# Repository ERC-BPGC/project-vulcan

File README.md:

# Project VULCAN

Project VULCAN is an open humanoid robotics platform focused on expressive human-robot interaction through modular mechanical, electronic, and AI-driven subsystems. It is a humanoid robot facial structure that can interact with humans — tracking faces, expressing emotions, hearing and speaking.

## Current Status

Actively undergoing infrastructure modernization and subsystem stabilization before next-generation expansion.

## Architecture Principles
* Atomic modular subsystems.
* Minimal cross-module interference.
* Hardware/software separation.
* Scalable pipelines for future contributors.
* Experiment isolation via `experiments/`.

## System Pipeline Overview

```text
 Microphone Input
        ↓
 Speech-to-Text
        ↓
 Emotion + Context Fusion
        ↓
 LLM / RAG Pipeline
        ↓
 Response Generation
        ↓
 TTS + Mouth Movement + Facial Expressions

```

## Features
* **Eyes** — Independent 2-axis eyeball motion, eyelids, and gaze tracking via embedded cameras.
* **Mouth** — Lip movement synced with speech and emotional expressions.
* **Eyebrows** — Up/down motion to complement expressions.
* **Neck** — 2-axis motion (horizontal 360° + vertical tilt).
* **Hearing & Speech** — Microphone array for sound localisation, speech recognition, and TTS output.
* **Vision** — Face detection, gaze estimation, emotion recognition (FER), hand-wave detection.
* **LLM Integration** — RAG-augmented responses via GPT.

## Demos

*(GIF previews of eye tracking, blinking, mouth articulation, and emotion response coming soon!)*

* [Eye, eyelid & eyebrow subsystem](https://www.youtube.com/watch?v=uqxhR49N3ws) — asymmetric eyeball motion with cameras, blinking, and brow movement.
* [Mouth subsystem](https://www.youtube.com/watch?v=Ke2lJfY4haM) — lip articulation for speech and emotion.
* [Neck subsystem](https://www.youtube.com/watch?v=GJRW8hP-Jcs) — full pan and tilt.

## Hardware Stack
* ESP32-CAM vision nodes.
* Arduino Mega servo controller.
* Custom servo PCB.
* Embedded microphones.
* Dual-camera eye subsystem.

## Subsystems

### Mechanical

* **Eye, eyelid & eyebrow subsystem** — asymmetric eyeball motion with cameras, blinking, and brow movement.
* **Mouth subsystem** — lip articulation for speech and emotion.
* **Neck subsystem** — full pan and tilt.

### Software

* **`software/vision/`** — face detection, gaze estimation (`t_gaze.py`), emotion recognition (`m_model.py`, `m_expression.py`), hand-wave detection.
* **`software/speech/`** — speech-to-text, TTS, voice selection.
* **`software/llm/`** — GPT interface and RAG pipeline for context-aware responses.
* **`software/core/`** — main driver (`vulcan.py`, `vulcan2.py`) coordinating all subsystems.

### Electronics

* **Servo PCB (ESP32 & Mega variants)** — custom KiCad boards in `electronics/pcb/`.
* **ESP32-CAM firmware** — `electronics/firmware/camera_esp/`.
* **Arduino servo firmware** — `electronics/firmware/serial_arduino/`.

## Repository Structure

```text
project-vulcan/
├── docs/                   # Install guides (CUDA, OpenCV, dlib), diagrams
├── software/
│   ├── core/               # Main entry points
│   ├── vision/             # CV modules
│   ├── speech/             # STT / TTS
│   ├── llm/                # GPT + RAG pipeline
│   │   └── rag/
│   ├── data/               # Knowledge base files for RAG
│   ├── utils/              # Shared helpers
│   ├── tools/              # Diagnostic scripts (check mic, list cameras)
│   ├── experiments/        # Prototypes and WIP scripts
│   ├── models/             # Model weights (gitignored — see models/README.md)
│   ├── archive/            # Deprecated code
│   └── requirements.txt
├── electronics/
│   ├── pcb/                # KiCad projects
│   ├── firmware/           # Arduino / ESP32 sketches
│   └── scripts/            # Python hardware-communication scripts
└── mechanical/             # CAD files (SolidWorks, Fusion, Blender, STL)
    ├── Eye_subsystem/
    ├── Mouth_Subsystem/
    ├── Head Structure/
    ├── Neck Base/
    └── base_holder/

```

> **Model weights** are not tracked in git — see ```software/models/README.md``` for download links. <br>
> **Install guides** for CUDA, OpenCV, and dlib are in ```docs/```

## Getting Started

```bash
# Install Python dependencies
pip install -r software/requirements.txt

# Download model weights (see software/models/README.md), then run
python software/core/vulcan2.py

```

## Contributor Guidelines

* New features should be isolated into modules.
* Avoid editing archived or legacy systems.
* Experimental work belongs in `software/experiments/`.
* Shared utilities belong in `software/utils/`.
* All hardware communication layers must remain abstracted.

## Roadmap

* ROS2 migration.
* Improved facial animation pipeline.
* Real-time multimodal emotion fusion.
* Autonomous interaction routines.
* Enhanced gaze tracking.
* Full conversational memory system.

## Built With

* [Python](https://www.python.org/)
* [OpenCV](https://opencv.org/)
* [dlib](http://dlib.net/)
* [LangChain](https://www.langchain.com/) / [OpenAI](https://openai.com/)
* [KiCad](https://www.kicad.org/)
* [ROS](https://www.ros.org/)

## Downloading all the dependencies for running auto folder
- Make sure cmake and cuda are already downloaded before doing this
- Download the reurequirements.txt file
- pip install -r requirements.txt

## Limitations

* The robot covers only the structure above the neck — no full-body mobility.

## Core Contributors

* [Parth Shah](https://github.com/Parth-Shah-Tool-Kit)
* [Ritwik Sharma](https://github.com/Maker-Rat)
* [Sharvil Potdar](https://github.com/CipherWielder1104)
* [Aryan Goyal]
* [Kevin B. Matthew]
* Indrajit Mandal
* [Anirudh Singh Air](https://github.com/bodsvei)
* [Ayush R. Srivastava]
* [Aditya Kushwaha](https://github.com/Adityakushwaha2006)
* [Vedant Vakharia](https://github.com/vedantvakharia)
* [Rajas Kasar]

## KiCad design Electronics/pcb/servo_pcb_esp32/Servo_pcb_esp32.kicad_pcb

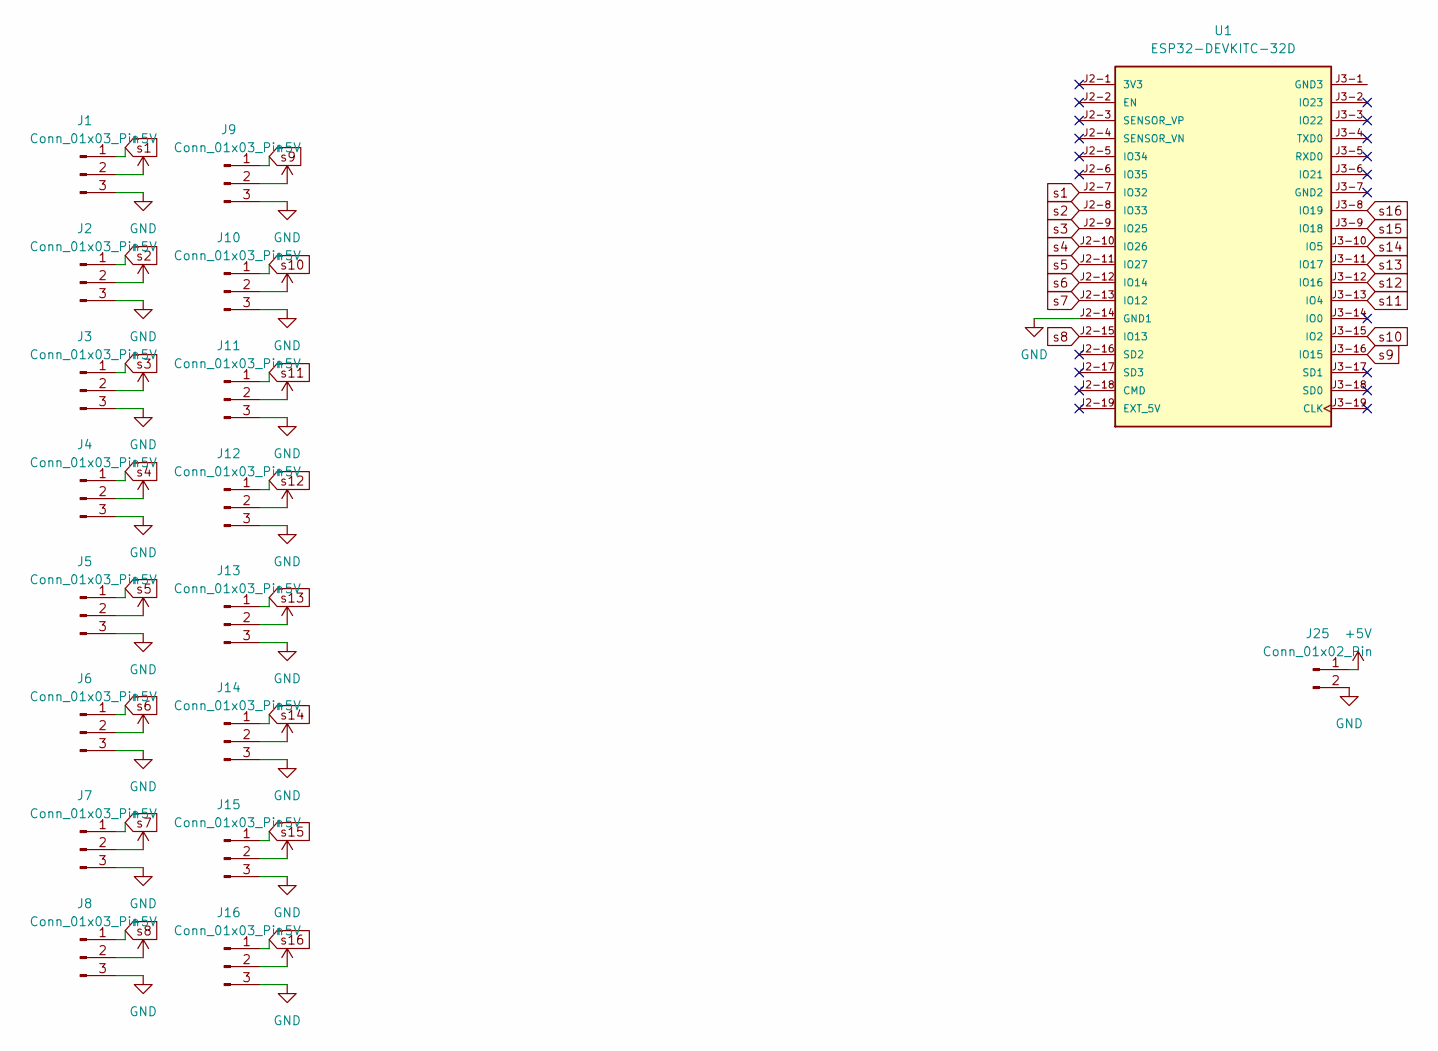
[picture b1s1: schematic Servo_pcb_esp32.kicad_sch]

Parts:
J1, J2, J3, J4, J5, J6, J7, J8, J9, J10, J11, J12, J13, J14, J15, J16: Conn_01x03_Pin; PinHeader_1x03_P2.54mm_Vertical
J25: Conn_01x02_Pin; AMASS_XT60-M_1x02_P7.20mm_Vertical
U1: ESP32-DEVKITC-32D; MODULE_ESP32-DEVKITC-32D; PARTREV V4

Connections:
+5V: J1.2, J2.2, J3.2, J4.2, J5.2, J6.2, J7.2, J8.2, J9.2, J10.2, J11.2, J12.2, J13.2, J14.2, J15.2, J16.2, J25.1
GND: J1.3, J2.3, J3.3, J4.3, J5.3, J6.3, J7.3, J8.3, J9.3, J10.3, J11.3, J12.3, J13.3, J14.3, J15.3, J16.3, J25.2, U1.J2-14 (GND1)
s1: J1.1, U1.J2-7 (IO32)
s2: J2.1, U1.J2-8 (IO33)
s3: J3.1, U1.J2-9 (IO25)
s4: J4.1, U1.J2-10 (IO26)
s5: J5.1, U1.J2-11 (IO27)
s6: J6.1, U1.J2-12 (IO14)
s7: J7.1, U1.J2-13 (IO12)
s8: J8.1, U1.J2-15 (IO13)
s9: J9.1, U1.J3-16 (IO15)
s10: J10.1, U1.J3-15 (IO2)
s11: J11.1, U1.J3-13 (IO4)
s12: J12.1, U1.J3-12 (IO16)
s13: J13.1, U1.J3-11 (IO17)
s14: J14.1, U1.J3-10 (IO5)
s15: J15.1, U1.J3-9 (IO18)
s16: J16.1, U1.J3-8 (IO19)

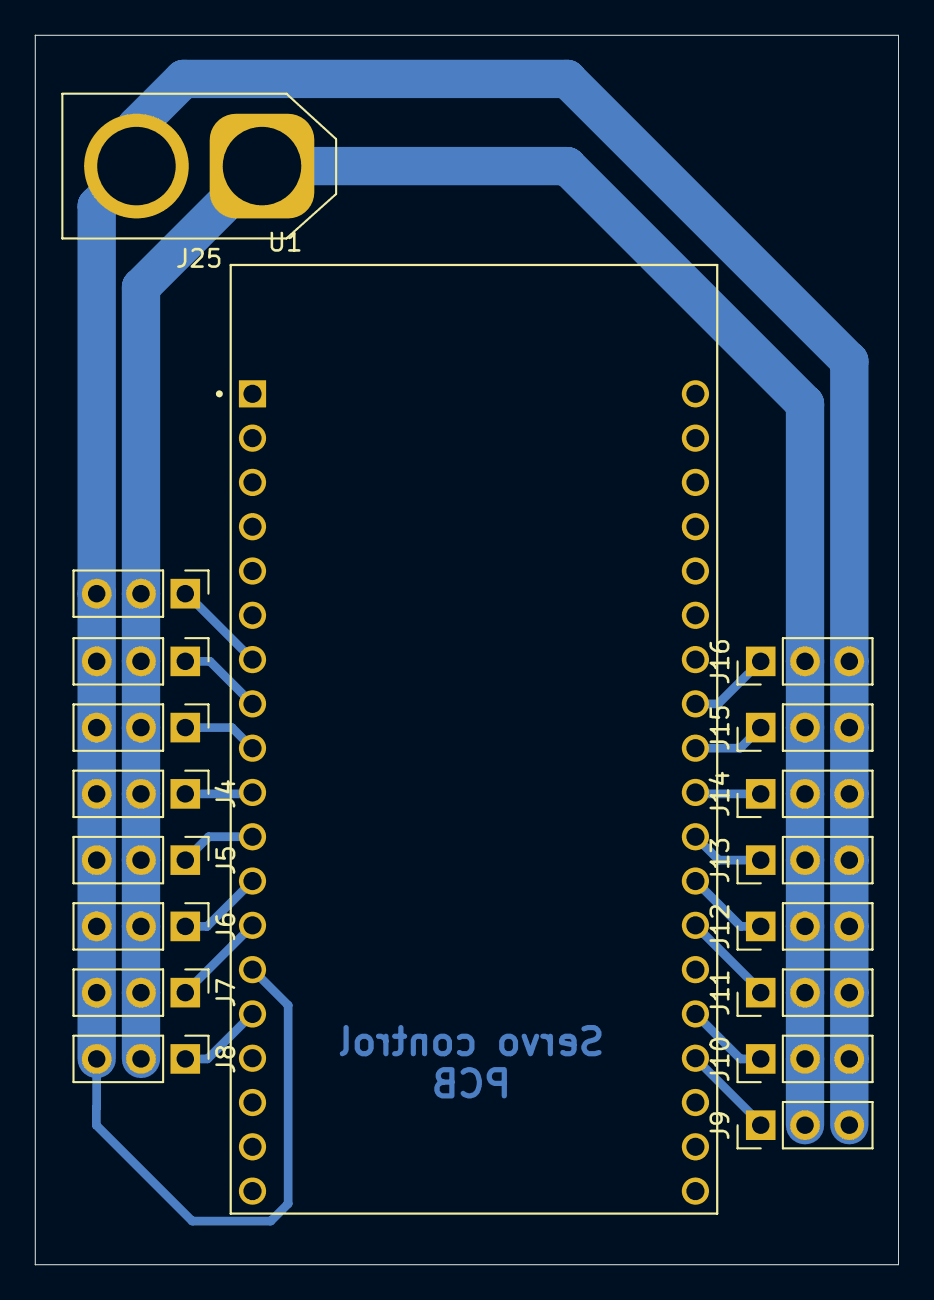
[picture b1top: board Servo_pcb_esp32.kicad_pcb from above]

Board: 2 copper layers, 49.5 x 70.5 mm, 18 parts (0 on the bottom side), 18 nets.

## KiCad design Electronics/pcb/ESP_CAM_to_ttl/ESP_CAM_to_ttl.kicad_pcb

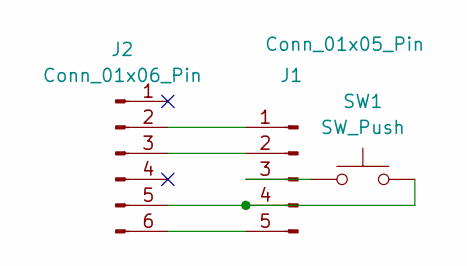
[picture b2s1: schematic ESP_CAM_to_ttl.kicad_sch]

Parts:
J1: Conn_01x05_Pin; PinHeader_1x05_P2.54mm_Vertical
J2: Conn_01x06_Pin; PinHeader_1x06_P2.54mm_Vertical
SW1: SW_Push; SW_SPST_CK_RS282G05A3

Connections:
unnamed: J1.1, J2.2
unnamed: J1.2, J2.3
unnamed: J1.3, SW1.1
unnamed: J1.4, J2.5, SW1.2
unnamed: J1.5, J2.6

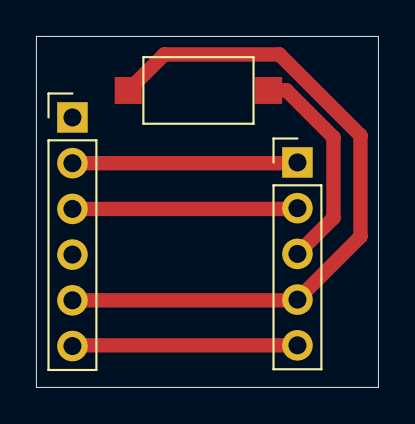
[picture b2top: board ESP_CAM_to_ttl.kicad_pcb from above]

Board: 2 copper layers, 19.0 x 19.5 mm, 3 parts (0 on the bottom side), 5 nets.

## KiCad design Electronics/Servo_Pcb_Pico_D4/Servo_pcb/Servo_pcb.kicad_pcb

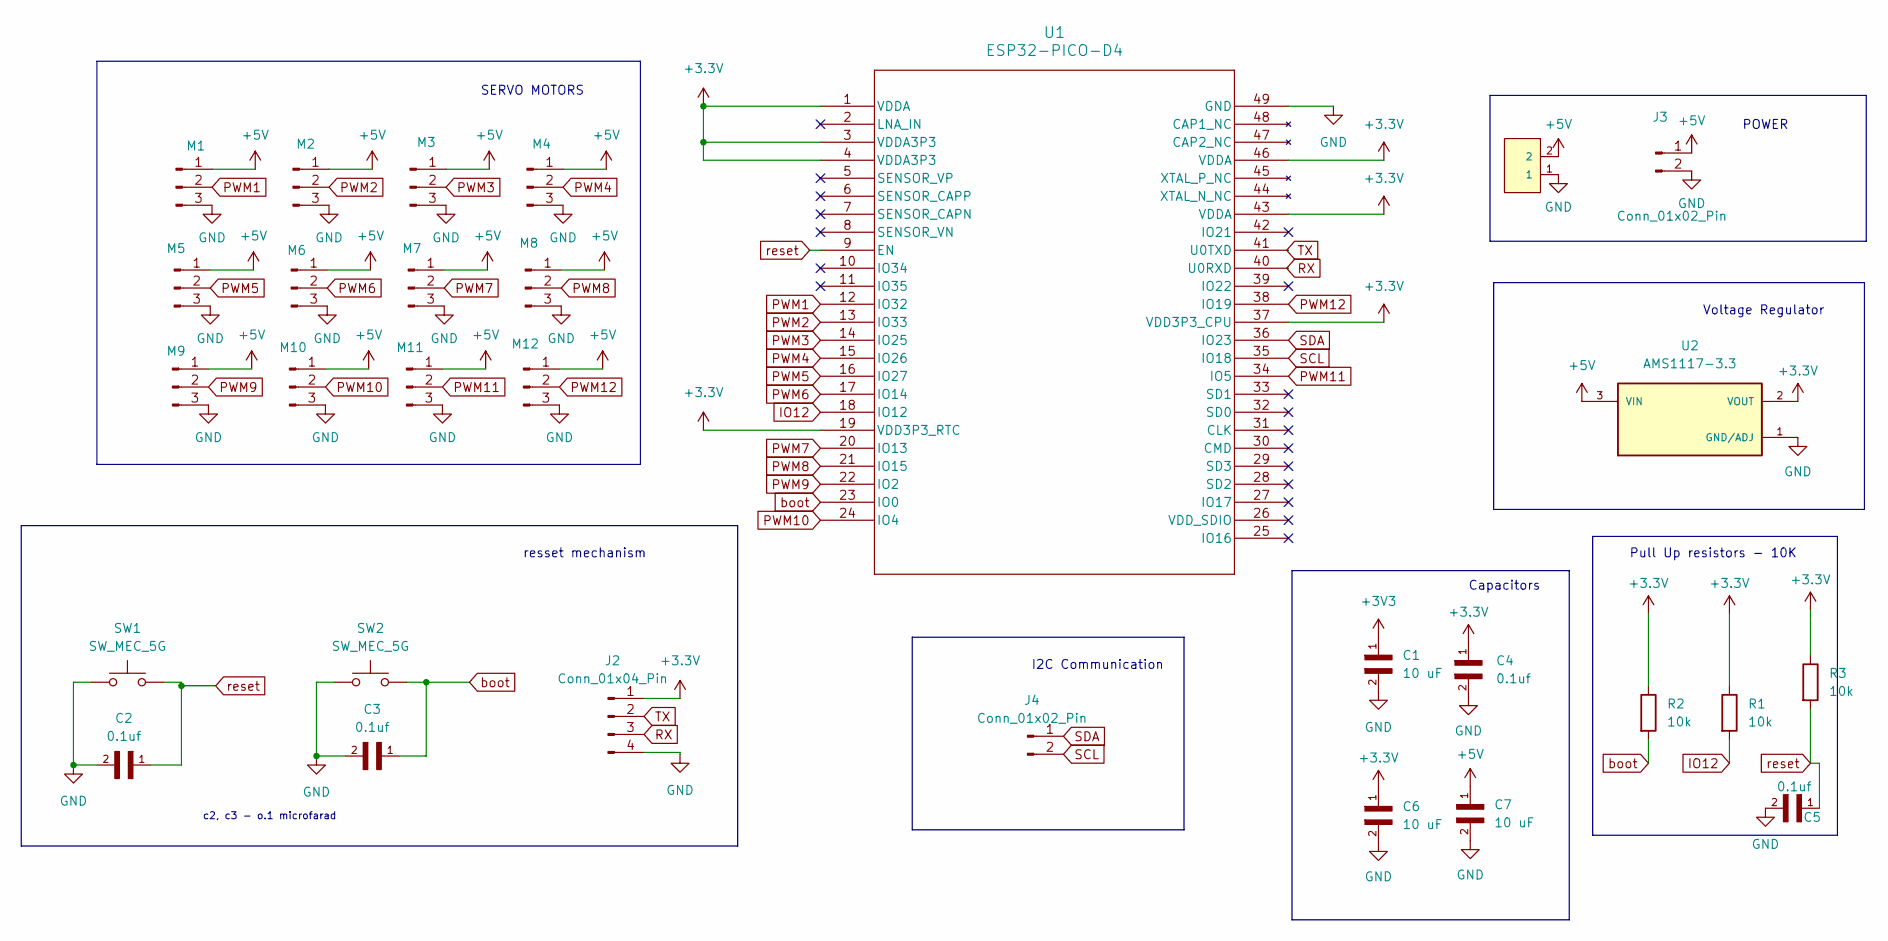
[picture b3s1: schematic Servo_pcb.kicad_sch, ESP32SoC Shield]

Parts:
C1, C6, C7: 10 uF; C_0402_1005Metric_Pad0.74x0.62mm_HandSolder
C2, C3, C4, C5: 0.1uf; C_0402_1005Metric_Pad0.74x0.62mm_HandSolder
J1: DCJ200-10-A-XX-K_REVA; AMASS_XT30U-M_1x02_P5.0mm_Vertical; PARTREV 1.2
J2: Conn_01x04_Pin; PinHeader_1x04_P1.27mm_Vertical
J3, J4: Conn_01x02_Pin; JST_XH_B2B-XH-A_1x02_P2.50mm_Vertical
M1, M2, M3, M4, M5, M6, M7, M8, M9, M10, M11, M12: Conn_01x03_Pin; PinHeader_1x03_P2.54mm_Vertical
R1, R2, R3: 10k; R_0603_1608Metric
SW1, SW2: SW_MEC_5G; SW_Tactile_SPST_NO_Straight_CK_PTS636Sx25SMTRLFS
U1: ESP32-PICO-D4; PQFN50P700X700X104-49N
U2: AMS1117-3.3; SOT229P700X180-4N; PARTREV N/A

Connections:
+5V: C7.1, J1.2, J3.1, M1.1, M2.1, M3.1, M4.1, M5.1, M6.1, M7.1, M8.1, M9.1, M10.1, M11.1, M12.1, U2.3 (VIN)
GND: C1.2, C2.2, C3.2, C4.2, C5.2, C6.2, C7.2, J1.1, J2.4, J3.2, M1.3, M2.3, M3.3, M4.3, M5.3, M6.3, M7.3, M8.3, M9.3, M10.3, M11.3, M12.3, SW1.1, SW2.1, U1.49 (GND), U2.1 (GND/ADJ)
IO12: R1.2, U1.18 (IO12)
PWM1: M1.2, U1.12 (IO32)
PWM2: M2.2, U1.13 (IO33)
PWM3: M3.2, U1.14 (IO25)
PWM4: M4.2, U1.15 (IO26)
PWM5: M5.2, U1.16 (IO27)
PWM6: M6.2, U1.17 (IO14)
PWM7: M7.2, U1.20 (IO13)
PWM8: M8.2, U1.21 (IO15)
PWM9: M9.2, U1.22 (IO2)
PWM10: M10.2, U1.24 (IO4)
PWM11: M11.2, U1.34 (IO5)
PWM12: M12.2, U1.38 (IO19)
RX: J2.3, U1.40 (U0RXD)
SCL: J4.2, U1.35 (IO18)
SDA: J4.1, U1.36 (IO23)
TX: J2.2, U1.41 (U0TXD)
boot: C3.1, R2.2, SW2.2, U1.23 (IO0)
reset: C2.1, C5.1, R3.2, SW1.2, U1.9 (EN)

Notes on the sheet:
I2C Communication
POWER
c2, c3 - o.1 microfarad
SERVO MOTORS
Voltage Regulator
Capacitors
resset mechanism
Pull Up resistors - 10K

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
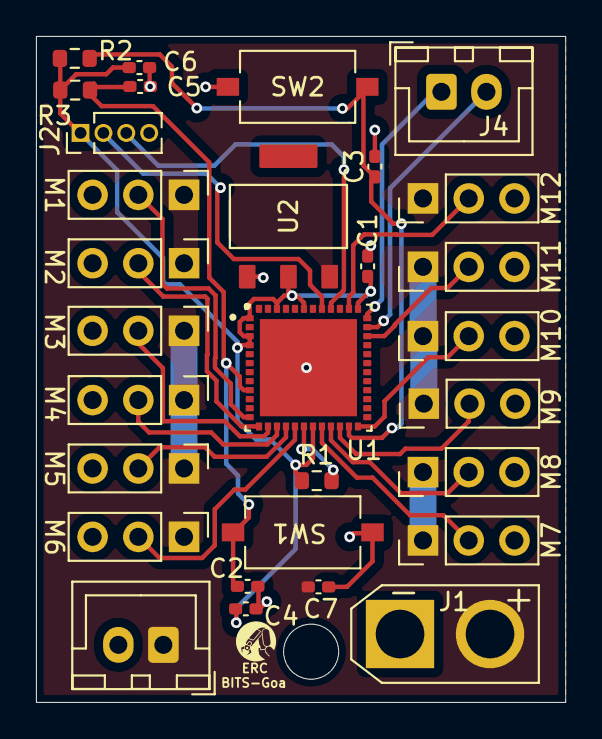
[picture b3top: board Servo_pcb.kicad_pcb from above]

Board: 2 copper layers, 29.4 x 37.0 mm, 31 parts (0 on the bottom side), 22 nets.

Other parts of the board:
R5: R; erc_logo_3mmx3mm

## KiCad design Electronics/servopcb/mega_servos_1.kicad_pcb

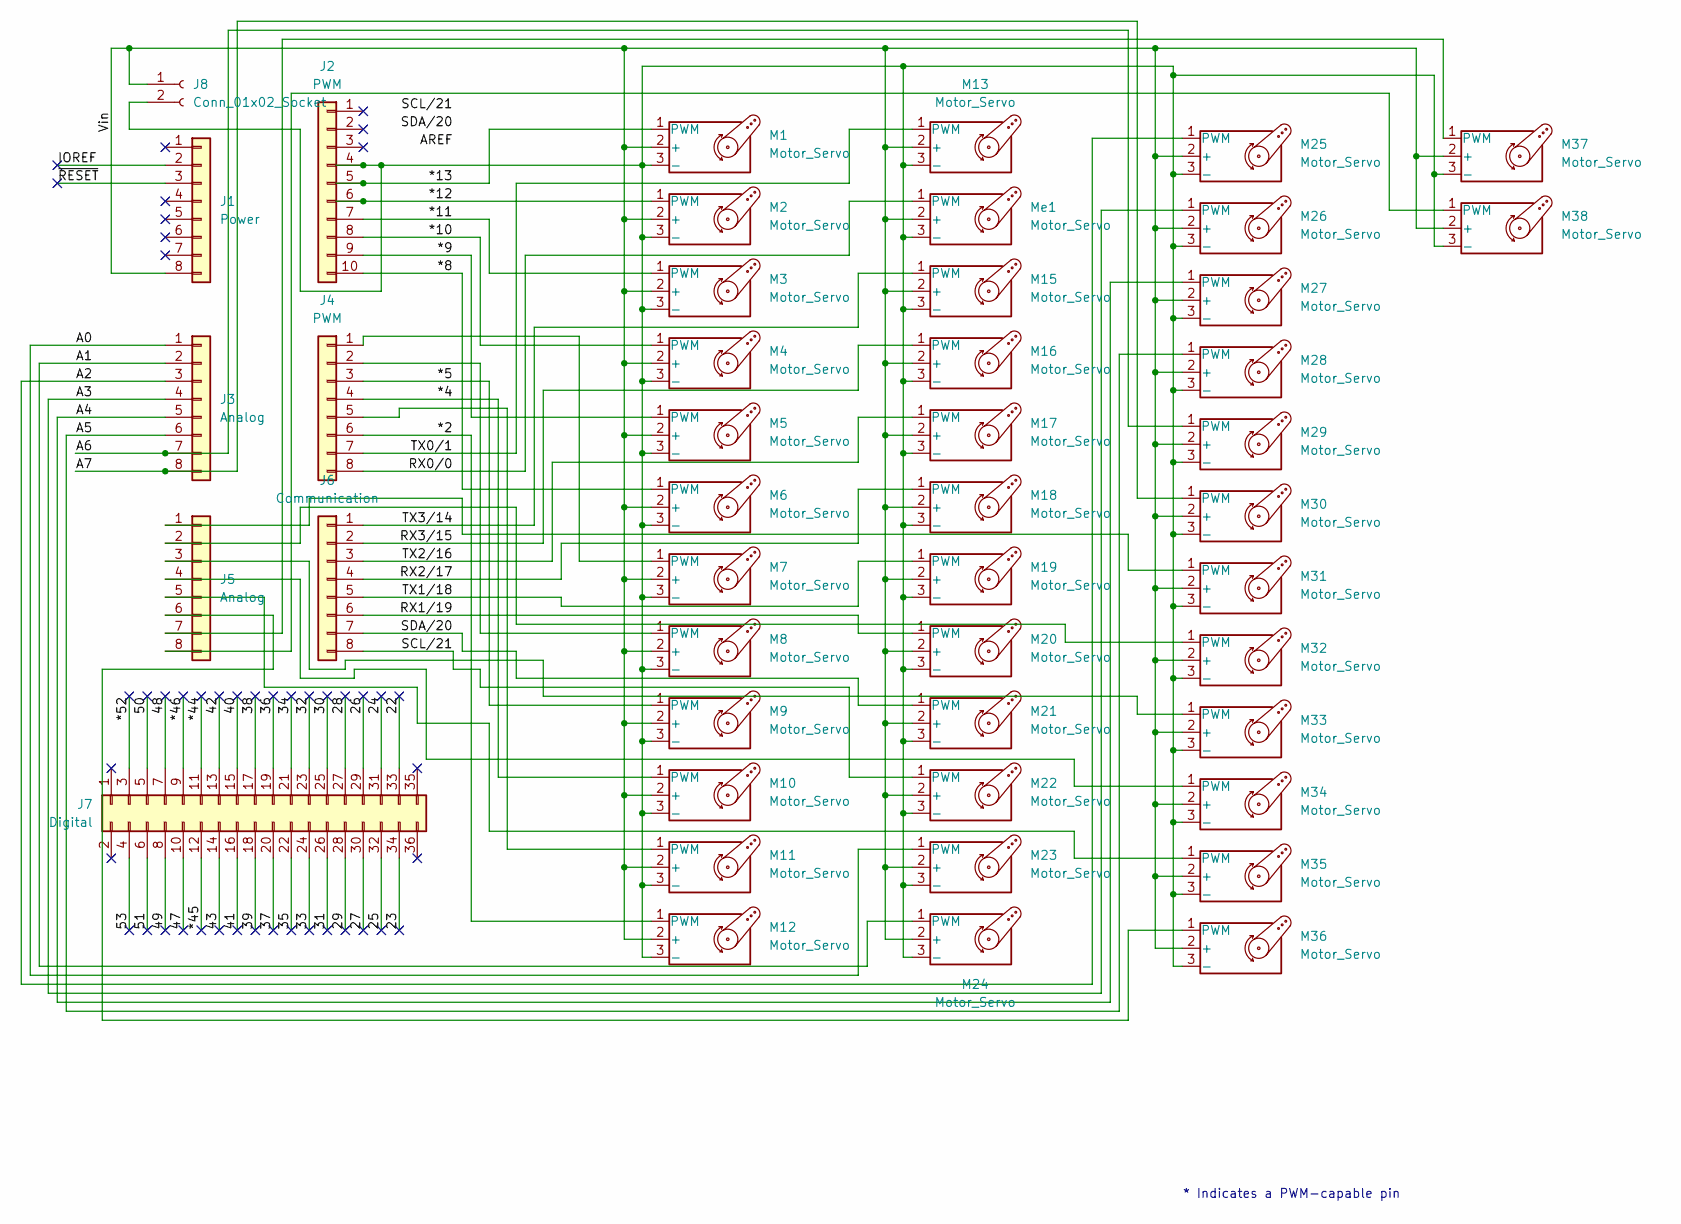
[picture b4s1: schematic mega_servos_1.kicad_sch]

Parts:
J1: Power; PinSocket_1x08_P2.54mm_Vertical
J2: PWM; PinSocket_1x10_P2.54mm_Vertical
J3, J5: Analog; PinSocket_1x08_P2.54mm_Vertical
J4: PWM; PinSocket_1x08_P2.54mm_Vertical
J6: Communication; PinSocket_1x08_P2.54mm_Vertical
J7: Digital; PinSocket_2x18_P2.54mm_Vertical
J8: Conn_01x02_Socket; AMASS_XT60-F_1x02_P7.20mm_Vertical
M1, M2, M3, M4, M5, M6, M7, M8, M9, M10, M11, M12, M13, M15, M16, M17, M18, M19, M20, M21, M22, M23, M24, M25, M26, M27, M28, M29, M30, M31, M32, M33, M34, M35, M36, M37, M38: Motor_Servo; PinHeader_1x03_P2.54mm_Vertical
Me1: Motor_Servo; PinHeader_1x03_P2.54mm_Vertical

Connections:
/22: J7.33
/23: J7.34
/24: J7.31
/25: J7.32
/26: J7.29
/27: J7.30
/28: J7.27
/29: J7.28
/30: J7.25
/31: J7.26
/32: J7.23
/33: J7.24
/34: J7.21
/35: J7.22
/36: J7.19
/37: J7.20
/38: J7.17
/39: J7.18
/40: J7.15
/41: J7.16
/42: J7.13
/43: J7.14
/47: J7.10
/48: J7.7
/49: J7.8
/50: J7.5
/51: J7.6
/53: J7.4
/*2: J4.6, M12.1 (PWM)
/*4: J4.4, M10.1 (PWM)
/*5: J4.3, M9.1 (PWM)
/*8: J2.10, M6.1 (PWM)
/*9: J2.9, M5.1 (PWM)
/*10: J2.8, M4.1 (PWM)
/*11: J2.7, M3.1 (PWM)
/*12: J2.6, M2.1 (PWM)
/*13: J2.5, M1.1 (PWM)
/*44: J7.11
/*45: J7.12
/*46: J7.9
/*52: J7.3
/A0: J3.1, M23.1 (PWM)
/A1: J3.2, M24.1 (PWM)
/A2: J3.3, M25.1 (PWM)
/A3: J3.4, M26.1 (PWM)
/A4: J3.5, M27.1 (PWM)
/A5: J3.6, M28.1 (PWM)
/A6: J3.7, M29.1 (PWM)
/A7: J3.8, M30.1 (PWM)
/IOREF: J1.2
/RX0/0: J4.8, Me1.1 (PWM)
/RX1/19: J6.6, M20.1 (PWM)
/RX2/17: J6.4, M18.1 (PWM)
/RX3/15: J6.2, M16.1 (PWM)
/SCL/21: J6.8, M22.1 (PWM)
/SDA/20: J6.7, M21.1 (PWM)
/TX0/1: J4.7, M13.1 (PWM)
/TX1/18: J6.5, M19.1 (PWM)
/TX2/16: J6.3, M17.1 (PWM)
/TX3/14: J6.1, M15.1 (PWM)
/Vin: J1.8, J8.1, M1.2 (+), M2.2 (+), M3.2 (+), M4.2 (+), M5.2 (+), M6.2 (+), M7.2 (+), M8.2 (+), M9.2 (+), M10.2 (+), M11.2 (+), M12.2 (+), M13.2 (+), M15.2 (+), M16.2 (+), M17.2 (+), M18.2 (+), M19.2 (+), M20.2 (+), M21.2 (+), M22.2 (+), M23.2 (+), M24.2 (+), M25.2 (+), M26.2 (+), M27.2 (+), M28.2 (+), M29.2 (+), M30.2 (+), M31.2 (+), M32.2 (+), M33.2 (+), M34.2 (+), M35.2 (+), M36.2 (+), M37.2 (+), M38.2 (+), Me1.2 (+)
/~RESET: J1.3
unnamed: J2.4, J8.2, M1.3 (-), M2.3 (-), M3.3 (-), M4.3 (-), M5.3 (-), M6.3 (-), M7.3 (-), M8.3 (-), M9.3 (-), M10.3 (-), M11.3 (-), M12.3 (-), M13.3 (-), M15.3 (-), M16.3 (-), M17.3 (-), M18.3 (-), M19.3 (-), M20.3 (-), M21.3 (-), M22.3 (-), M23.3 (-), M24.3 (-), M25.3 (-), M26.3 (-), M27.3 (-), M28.3 (-), M29.3 (-), M30.3 (-), M31.3 (-), M32.3 (-), M33.3 (-), M34.3 (-), M35.3 (-), M36.3 (-), M37.3 (-), M38.3 (-), Me1.3 (-)
unnamed: J4.1, M7.1 (PWM)
unnamed: J4.2, M8.1 (PWM)
unnamed: J4.5, M11.1 (PWM)
unnamed: J5.1, M31.1 (PWM)
unnamed: J5.2, M32.1 (PWM)
unnamed: J5.3, M33.1 (PWM)
unnamed: J5.4, M34.1 (PWM)
unnamed: J5.5, M35.1 (PWM)
unnamed: J5.6, M36.1 (PWM)
unnamed: J5.7, M37.1 (PWM)
unnamed: J5.8, M38.1 (PWM)

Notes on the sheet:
* Indicates a PWM-capable pin

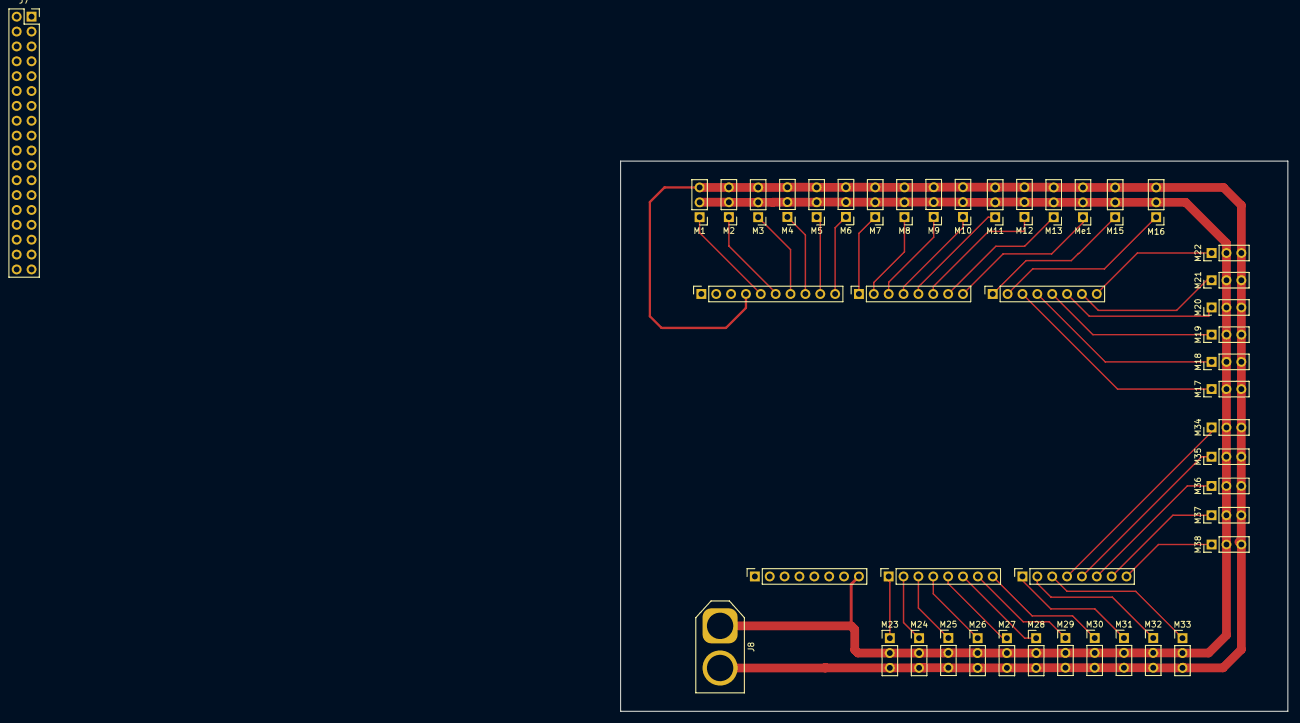
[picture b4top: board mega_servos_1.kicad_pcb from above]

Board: 2 copper layers, 114.0 x 94.0 mm, 46 parts (0 on the bottom side), 40 nets.

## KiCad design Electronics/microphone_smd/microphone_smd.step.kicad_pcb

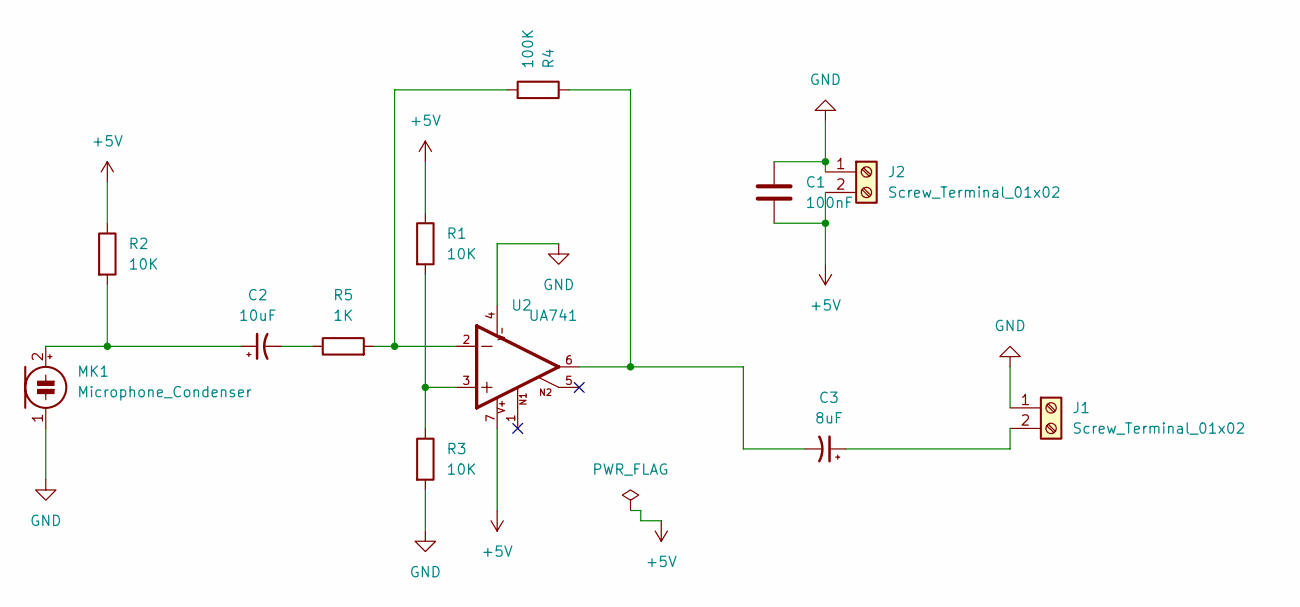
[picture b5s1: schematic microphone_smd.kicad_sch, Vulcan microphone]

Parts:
C1: 100nF; C_Disc_D3.0mm_W1.6mm_P2.50mm
C2: 10uF; CP_Radial_D8.0mm_P5.00mm
C3: 8uF; CP_Radial_D8.0mm_P5.00mm
J1, J2: Screw_Terminal_01x02; PinHeader_1x02_P2.54mm_Vertical
MK1: Microphone_Condenser; PinHeader_1x02_P2.54mm_Vertical
R1, R2, R3: 10K; R_Axial_DIN0207_L6.3mm_D2.5mm_P10.16mm_Horizontal
R4: 100K; R_Axial_DIN0207_L6.3mm_D2.5mm_P10.16mm_Horizontal
R5: 1K; R_Axial_DIN0207_L6.3mm_D2.5mm_P10.16mm_Horizontal
U2: UA741; DIP-8_W10.16mm

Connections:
+5V: C1.2, J2.2, R1.1, R2.1, U2.7
GND: C1.1, J1.1, J2.1, MK1.1 (-), R3.2, U2.4
unnamed: C2.2, R5.1
unnamed 3: C3.2, R4.1, U2.6; also elsewhere on the board
unnamed 5: C3.1, J1.2; also elsewhere on the board
unnamed: C2.1, MK1.2 (+), R2.2
unnamed: R1.2, R3.1, U2.3
unnamed: R4.2, R5.2, U2.2

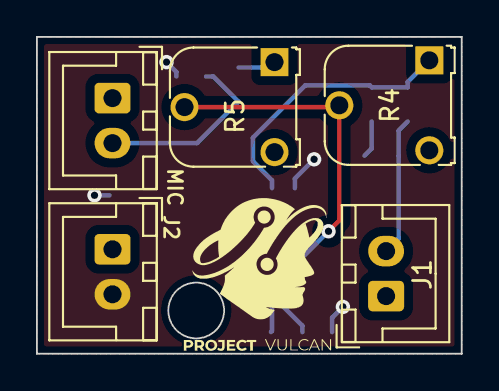
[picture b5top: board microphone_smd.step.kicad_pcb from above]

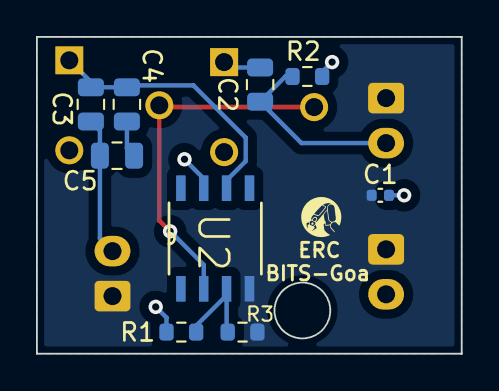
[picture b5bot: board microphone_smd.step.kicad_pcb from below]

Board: 2 copper layers, 23.6 x 17.6 mm, 14 parts (9 on the bottom side), 9 nets.

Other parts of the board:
C4: 10uF; C_0805_2012Metric
C5: 4.7uF; C_0805_2012Metric

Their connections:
unnamed 3: C4.2; also elsewhere on the board
unnamed: C4.1, C5.2
unnamed 5: C5.1; also elsewhere on the board

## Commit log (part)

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2024-04-12 Create gaze.py
    Face Tracking, Eye Tracking and Confidence Score. This is saved with timestamp in text file
2024-04-25 Necessary kicad files
2024-04-25 xt60
2024-04-27 out of MANA
    LoL simp
2024-04-27 added a new section in ReadMe file for individual code description
2024-04-27 changes in readme
2024-04-27 changes in individual code description
2024-05-26 test change
2024-05-28 Added Electronics
2024-05-28 Cleaned Auto
2024-05-28 Added mech
2024-05-30 Added gaze model file
2024-06-27 Updated paths
2024-06-27 path
2024-06-28 added cuda setup for linux doc
2024-06-28 added cuda setup doc
2024-06-28 Made gaze modular
2024-07-01 Updated Face and Gaze detection modular code with driver
2024-07-01 Added expression modular code and improvised on face recognition
2024-07-04 added hand background
2024-07-04 added some files
2024-07-04 removed key
2024-07-04 removed api key
2024-07-05 Restructed auto folder
2024-07-05 Added trigger1:b_Hand_waving_Detection
2024-07-05 dat file
2024-07-05 Added triggers
2024-07-05 added b_gaze
2024-07-05 tried b_speech_to_text
2024-07-06 Added sppech recog in background
2024-07-08 Added gpt suppport with internal communication
2024-07-08 some renames
2024-07-09 Some debugging in b_gpt
2024-07-09 looped print bug in b_gpt fixed
2024-07-11 Modified b_speech_to_text to send relevent data
2024-07-12 added b_TTS
2024-07-13 Fixed transmission bug 1
2024-07-13 Fixed communication bug 1/2
2024-07-13 fixed communcation bug 1/2
2024-07-14 Fixed communication bug 2/2
2024-08-13 added uv
2024-08-13 Update EyeSubSystem to accomodate new metal UV
2024-08-15 microphone pcb
2024-08-15 smd_microphone
2024-08-16 Added New Mouth Files and STLs Mech/Mouth_Subsystem/Solidworks/jaw/servofinal[1].SLDPRT
2024-08-16 Added Mouth_and_Eye_Subsystem Combined Base STL file.
2024-08-20 modified metal base and uv holder
2024-08-20 added stl files for uvholder and eye base
2024-09-03 Upadted upper and lower lower_eye_lid
2024-09-03 sorted blend files
2024-09-03 added pico file
2024-09-04 added new stl files of new eyelids
2024-09-04 updated upper eyelid
2024-09-10 Fine tuned tolerences
2024-09-12 Added ModelV4 size adjusted blend file in Head Structure
2024-09-12 Molds folder made
2024-09-14 added new files mech
2024-09-15 Added Full Face Model
2024-09-21 added new pcb servopcb for esp wroom 32
2024-09-21 Added 3FaceMould Blend File and STLs
2024-10-18 modified eye and mouth
2024-10-19 modified Mouth_Subsystem
2024-10-19 Modified teeth
2024-10-19 modified lower Lower_Jaw_Plate
2024-10-20 mouth
2024-10-20 Mouth_Subsystem
2024-10-20 Final mouth i guesss
2024-10-21 final mouth
2024-10-25 some minor edit
2024-10-25 new eye starts
2024-10-25 new eye version
2024-10-26 Added new eye ball_for_pusher_rod
2024-10-26 pusher_rod
2024-10-26 new push rod mechnism
2024-10-26 new push rods
2024-11-02 new eye subsystem with pla push rods
2024-11-02 head v5
2024-11-02 added new files
2024-11-03 eye+mouth
2024-11-05 modified pushrods
2024-11-05 modified mouth and eye
2024-11-05 CustomSKullV1
2024-11-07 some bullcrap done
2024-11-09 final Eye_subsystem
2024-11-09 Added filled Eyelids
2024-11-11 modified upper eye lid
2024-11-11 added eye lids push rods
2024-11-14 added cmaera code for esp cam module
2024-11-15 camera pcb file
2024-11-17 cam code and some small meye and mouth mod
2024-11-18 Lower jaw plate
2024-11-18 Skull other parts and pieces added
2024-11-19 Added base
2024-11-22 bruh a lot
2024-11-22 servo code
2024-11-29 last commit
2025-01-09 Fixes in mesh
2025-01-15 Update how to install cuda for cv2, dlib,torch,tensorflow for ubuntu22
2025-01-18 SKIN_FACE model added
2025-01-19 modified mouth
2025-01-19 muth better p1
2025-01-19 muth better p2
2025-01-21 modified lower base plate
2025-01-25 modified sliding servo
2025-01-25 New trial skull again
2025-02-04 added old mouth mech
2025-02-04 modified for better long mouth mech
2025-02-06 made better older mouth mech
2025-02-06 modified electironcs as per new hardware
2025-02-06 yawn
2025-02-06 mofified limits
2025-02-14 auto completed
2025-02-24 New mould for 2mm
2025-02-25 Cap for Face_2mm seperated and added
2025-11-05 Add installation instructions for dependencies
    Added installation command for auto folder dependencies.
2026-03-17 servo changes
2026-05-28 Update README with project details and structure
    Expanded project description and added architecture principles, system pipeline overview, features, demos, hardware stack, repository structure, getting started instructions, contributor guidelines, 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
2026-06-27 Add GitHub links for contributors
    Updated GitHub links for contributors Aditya Kushwaha and Vedant Vakharia.
